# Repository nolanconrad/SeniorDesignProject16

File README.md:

# SeniorDesignProject16
A general area for the code of the Project 16: The Human Cooler

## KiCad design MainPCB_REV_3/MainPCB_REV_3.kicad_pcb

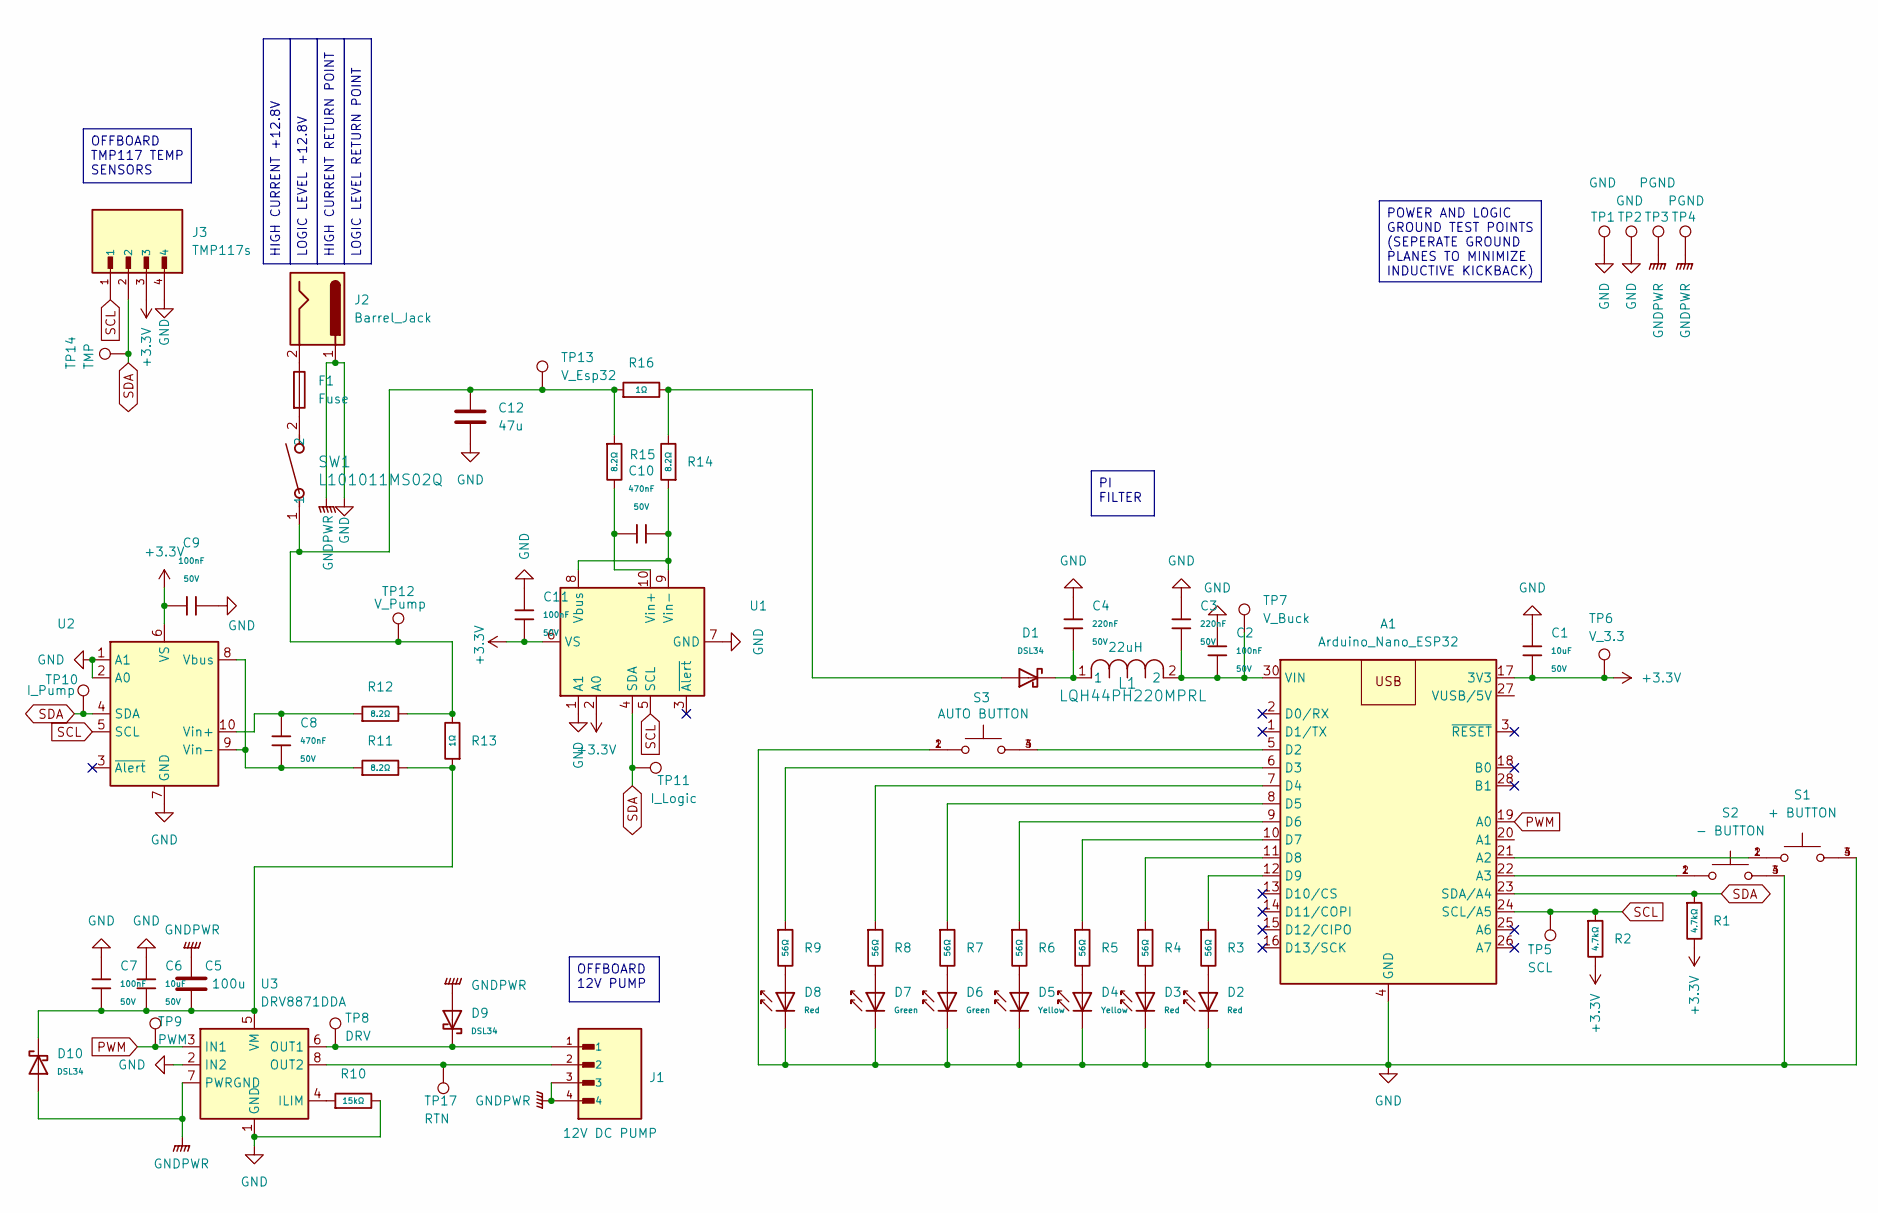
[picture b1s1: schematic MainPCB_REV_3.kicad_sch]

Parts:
A1: Arduino_Nano_ESP32; Arduino_Nano
C1, C6: 10uF; C_1206; Voltage Rated 50V; Tolerance ±10%; Part CL31A106KBHNNNE; LCSC C13585
C2, C7, C9, C11: 100nF; C_1206; Voltage Rated 50V; Tolerance ±10%; Part CL31B104KBCNNNC; LCSC C24497
C3, C4: 220nF; C_1206; Voltage Rated 50V; Tolerance ±10%; Part 1206B224K500NT; LCSC C1857
C5: 100u; CP_Radial_D5.0mm_P2.00mm
C8, C10: 470nF; C_0805; Voltage Rated 50V; Tolerance ±10%; Part CL21B474KBFNNNE; LCSC C13967
C12: 47u; CP_Radial_D5.0mm_P2.00mm
D1, D9, D10: DSL34; D_SOD-123FL; Part DSL34; LCSC C22466347
D2, D3, D8: Red; D_0805; Forward Voltage (VF) 1.6V~2.6V; Part NCD0805R1; LCSC C84256
D4, D5: Yellow; D_0805; Part KT-0805Y; LCSC C2296
D6, D7: Green; D_0805; Part KT-0805G; LCSC C2297
F1: Fuse; FUSE_658_LTF
J1: 12V DC PUMP; JST_S4B-PH-SM4-TB
J2: Barrel_Jack; BarrelJack_CUI_PJ-079BH_Horizontal
J3: TMP117s; JST_S4B-PH-SM4-TB
L1: LQH44PH220MPRL; IND_LQH44PN_PR_MUR
R1, R2: 4.7kΩ; R_1206; Overload Voltage (Max) 200V; Tolerance ±1%; Part 1206W4F4701T5E; LCSC C17936
R3, R4, R5, R6, R7, R8, R9: 56Ω; R_0805; Overload Voltage (Max) 150V; Tolerance ±1%; Part 0805W8F560JT5E; LCSC C17757
R10: 15kΩ; R_0805; Overload Voltage (Max) 150V; Tolerance ±1%; Part 0805W8F1502T5E; LCSC C17475
R11, R12, R14, R15: 8.2Ω; R_1206; Overload Voltage (Max) 200V; Tolerance ±1%; Part 1206W4F100JT5E; LCSC C17903
R13, R16: 1Ω; R_1206; Overload Voltage (Max) 200V; Tolerance ±1%; Part 1206W4F100KT5E; LCSC C17928
S1: + BUTTON; SW_TL3315NF250Q
S2: - BUTTON; SW_TL3315NF250Q
S3: AUTO BUTTON; SW_TL3315NF250Q
SW1: L101011MS02Q; SW_1MS02Q_CNK
TP1, TP2: GND; TestPoint_THTPad_D1.5mm_Drill0.7mm
TP3, TP4: PGND; TestPoint_THTPad_D1.5mm_Drill0.7mm
TP5: SCL; TestPoint_THTPad_D1.5mm_Drill0.7mm
TP6: V_3.3; TestPoint_THTPad_D1.5mm_Drill0.7mm
TP7: V_Buck; TestPoint_THTPad_D1.5mm_Drill0.7mm
TP8: DRV; TestPoint_THTPad_D1.5mm_Drill0.7mm
TP9: PWM; TestPoint_THTPad_D1.5mm_Drill0.7mm
TP10: I_Pump; TestPoint_THTPad_D1.5mm_Drill0.7mm
TP11: I_Logic; TestPoint_THTPad_D1.5mm_Drill0.7mm
TP12: V_Pump; TestPoint_THTPad_D1.5mm_Drill0.7mm
TP13: V_Esp32; TestPoint_THTPad_D1.5mm_Drill0.7mm
TP14: TMP; TestPoint_THTPad_D1.5mm_Drill0.7mm
TP17: RTN; TestPoint_THTPad_D1.5mm_Drill0.7mm
U1, U2: INA226; TSSOP-10_3x3mm_P0.5mm
U3: DRV8871DDA; Texas_HTSOP-8-1EP_3.9x4.9mm_P1.27mm_EP2.95x4.9mm_Mask2.4x3.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

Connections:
+3.3V: A1.17 (3V3), C1.2, C9.2, C11.2, J3.3, R1.2, R2.2, TP6.1 (1_1), U1.2 (A0), U1.6 (VS), U2.6 (VS)
GND: A1.4 (GND), A1.29 (GND), C1.1, C2.1, C3.1, C4.1, C5.2, C6.1, C7.1, C9.1, C11.1, C12.2, D2.1, D3.1, D4.1, D5.1, D6.1, D7.1, D8.1, D9.2, D10.2, J1.3, J1.4, J2.1, J3.4, R10.2, S1.3, S1.4, S2.3, S2.4, S3.1, S3.2, TP1.1 (1_1), TP2.1 (1_1), TP3.1 (1_1), TP4.1 (1_1), U1.1 (A1), U1.7 (GND), U2.1 (A1), U2.2 (A0), U2.7 (GND), U3.1 (GND), U3.2 (IN2), U3.7 (PWRGND), U3.9 (GND)
unnamed: A1.21 (A2), S1.1, S1.2
unnamed: A1.22 (A3), S2.1, S2.2
unnamed: A1.5 (D2), S3.3, S3.4
unnamed: A1.6 (D3), R9.1
unnamed: A1.7 (D4), R8.1
unnamed: A1.8 (D5), R7.1
unnamed: A1.9 (D6), R6.1
unnamed: A1.10 (D7), R5.1
unnamed: A1.11 (D8), R4.1
unnamed: A1.12 (D9), R3.1
unnamed: A1.30 (VIN), C2.2, C3.2, L1.2, TP7.1 (1_1)
unnamed: C4.2, D1.1, L1.1
unnamed: C12.1, R12.2, R13.2, R15.1, R16.1, SW1.1, TP12.1 (1_1), TP13.1 (1_1)
unnamed: D1.2, R14.2, R16.2
unnamed: D2.2, R3.2
unnamed: D3.2, R4.2
unnamed: D4.2, R5.2
unnamed: D5.2, R6.2
unnamed: D6.2, R7.2
unnamed: D7.2, R8.2
unnamed: D8.2, R9.2
unnamed: F1.1, J2.2
unnamed: F1.2, SW1.2
unnamed: C10.2, R14.1, U1.8 (Vbus), U1.9 (Vin-)
unnamed: C10.1, R15.2, U1.10 (Vin+)
unnamed: C8.2, R11.1, U2.8 (Vbus), U2.9 (Vin-)
unnamed: C8.1, R12.1, U2.10 (Vin+)
unnamed: R10.1, U3.4 (ILIM)
unnamed: D9.1, J1.1, TP8.1 (1_1), U3.6 (OUT1)
unnamed: J1.2, TP17.1 (1_1), U3.8 (OUT2)
unnamed: C5.1, C6.2, C7.2, D10.1, R11.2, R13.1, U3.5 (VM)
PWM: A1.19 (A0), TP9.1 (1_1), U3.3 (IN1)
SCL: A1.24 (SCL/A5), J3.1, R2.1, TP5.1 (1_1), U1.5 (SCL), U2.5 (SCL)
SDA: A1.23 (SDA/A4), J3.2, R1.1, TP10.1 (1_1), TP11.1 (1_1), TP14.1 (1_1), U1.4 (SDA), U2.4 (SDA)

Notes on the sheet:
PI FILTER
LOGIC LEVEL +12.8V
HIGH CURRENT RETURN POINT
HIGH CURRENT +12.8V
POWER AND LOGIC GROUND TEST POINTS (SEPERATE GROUND PLANES TO MINIMIZE INDUCTIVE KICKBACK)
OFFBOARD 12V PUMP
LOGIC LEVEL RETURN POINT
OFFBOARD TMP117 TEMP SENSORS

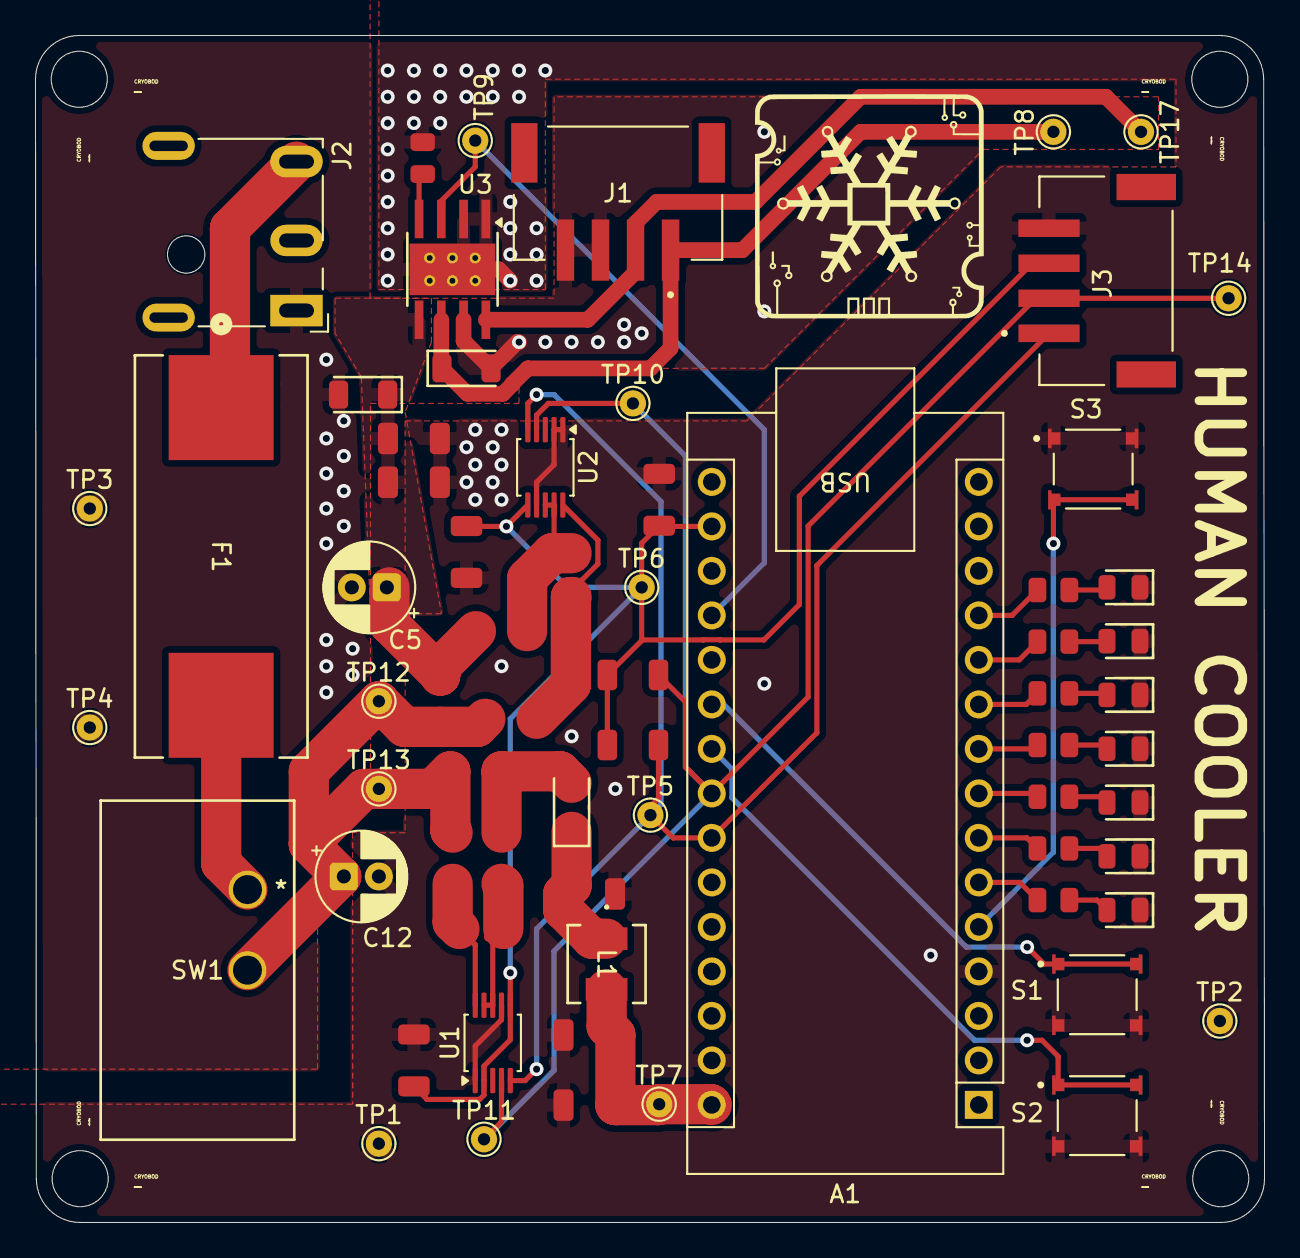
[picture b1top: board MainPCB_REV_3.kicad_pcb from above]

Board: 2 copper layers, 70.2 x 67.8 mm, 66 parts (0 on the bottom side), 36 nets.

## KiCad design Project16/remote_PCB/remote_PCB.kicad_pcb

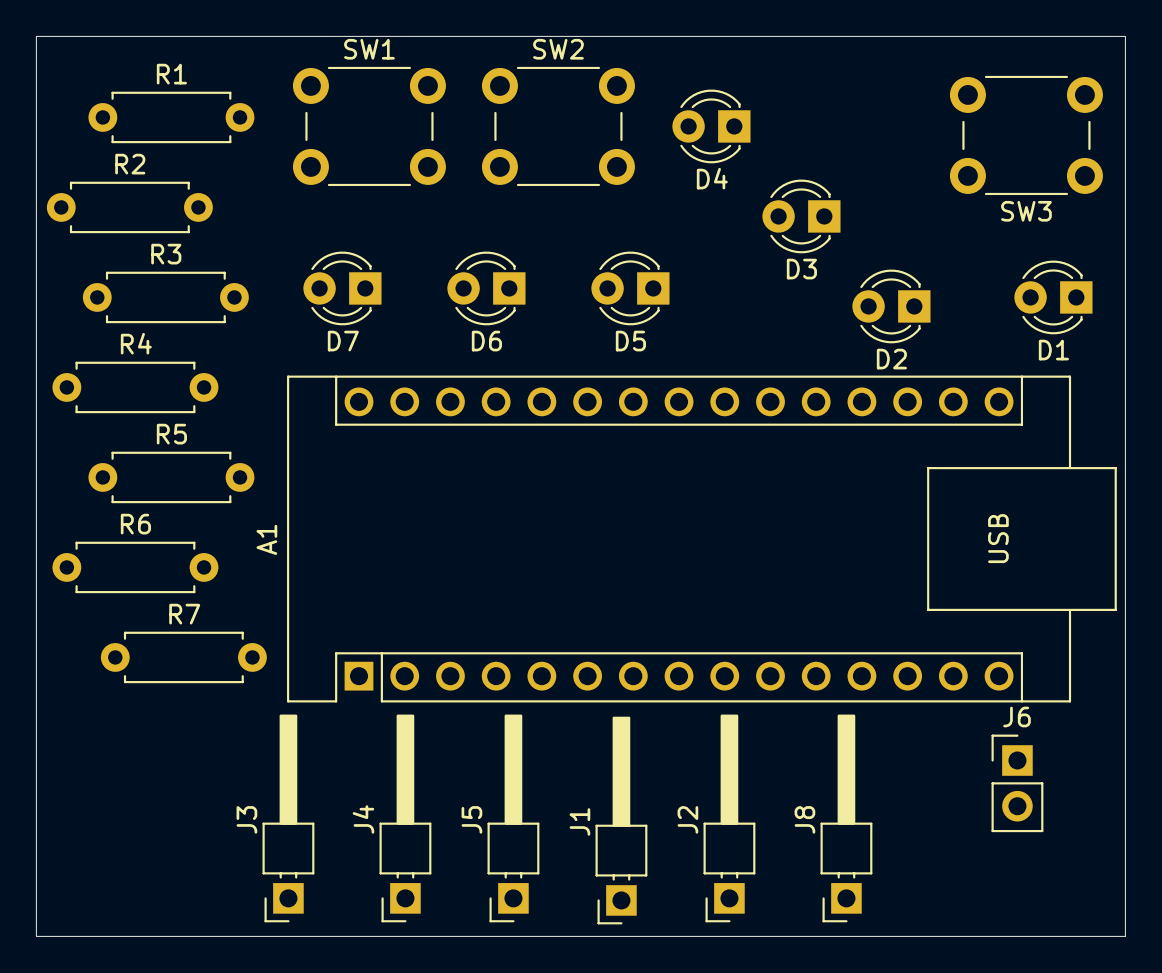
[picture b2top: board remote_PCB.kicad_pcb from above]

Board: 2 copper layers, 60.5 x 50.0 mm, 25 parts (0 on the bottom side), 25 nets, no tracks yet.

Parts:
A1: Arduino_Nano_ESP32; Arduino_Nano
D1: LED Auto; LED_D3.0mm
D2: BAT3; LED_D3.0mm
D3: BAT2; LED_D3.0mm
D4: BAT1; LED_D3.0mm
D5: MAN 3; LED_D3.0mm
D6: MAN 2; LED_D3.0mm
D7: MAN 1; LED_D3.0mm
J1, J2: i2c line; PinHeader_1x01_P2.54mm_Horizontal
J3: Vin; PinHeader_1x01_P2.54mm_Horizontal
J4: VUSB/5V; PinHeader_1x01_P2.54mm_Horizontal
J5: RESET; PinHeader_1x01_P2.54mm_Horizontal
J6: Motor Driver; PinHeader_1x02_P2.54mm_Vertical
J8: Current Sensor; PinHeader_1x01_P2.54mm_Horizontal
R1, R2, R3, R4, R5, R6, R7: R; R_Axial_DIN0207_L6.3mm_D2.5mm_P7.62mm_Horizontal
SW1: Man+; SW_PUSH_6mm
SW2: Man-; SW_PUSH_6mm
SW3: Auto ON/OFF; SW_PUSH_6mm

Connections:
/i2c tmp: A1.5 (D2), A1.6 (D3), J1.1, J2.1
unnamed: A1.19 (A0), J6.2
unnamed: A1.20 (A1), J6.1
unnamed: A1.21 (A2), J8.1
unnamed: A1.25 (A6), SW2.1
unnamed: A1.26 (A7), SW1.2
unnamed: A1.7 (D4), R7.1
unnamed: A1.8 (D5), R6.1
unnamed: A1.9 (D6), R5.1
unnamed: A1.10 (D7), R4.1
unnamed: A1.11 (D8), R3.1
unnamed: A1.12 (D9), R2.1
unnamed: A1.13 (D10/CS), R1.1
unnamed: A1.24 (SCL/A5), SW3.1
unnamed: A1.30 (VIN), J3.1
unnamed: A1.27 (VUSB/5V), J4.1
unnamed: A1.3 (~RESET), J5.1
unnamed: D1.2 (A), R1.2
unnamed: A1.4 (GND), A1.29 (GND), D1.1 (K), D2.1 (K), D3.1 (K), D4.1 (K), D5.1 (K), D6.1 (K), D7.1 (K), SW1.1, SW2.2, SW3.2
unnamed: D2.2 (A), R2.2
unnamed: D3.2 (A), R3.2
unnamed: D4.2 (A), R4.2
unnamed: D5.2 (A), R5.2
unnamed: D6.2 (A), R6.2
unnamed: D7.2 (A), R7.2

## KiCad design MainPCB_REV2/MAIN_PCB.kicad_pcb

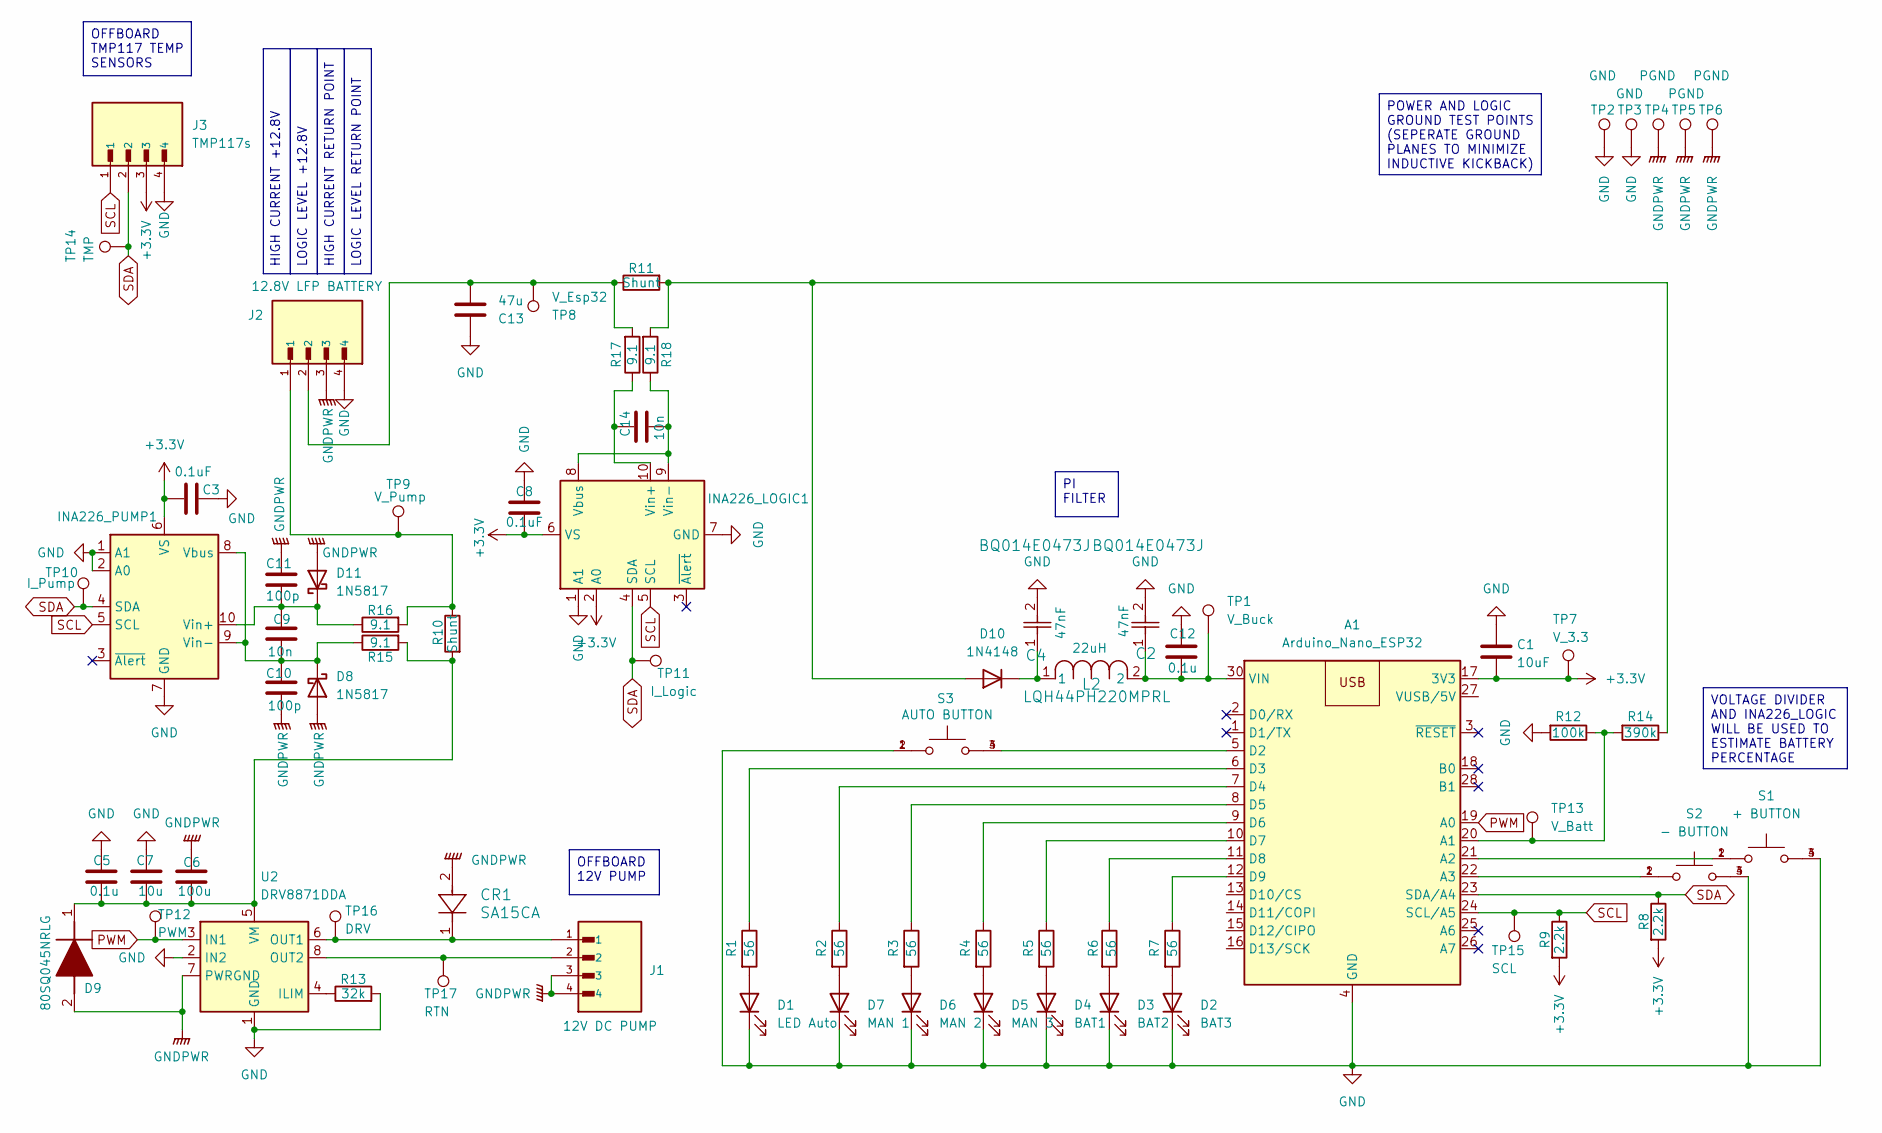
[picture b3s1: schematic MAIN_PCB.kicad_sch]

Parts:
A1: Arduino_Nano_ESP32; Arduino_Nano
C1: 10uF; CP_Radial_D5.0mm_P2.00mm
C2, C4: BQ014E0473J; CAP_BF01_AVX
C3, C8: 0.1uF; CAP_BF01_AVX
C5, C12: 0.1u; CAP_BF01_AVX
C6: 100u; CP_Radial_D5.0mm_P2.00mm
C7: 10u; CP_Radial_D5.0mm_P2.00mm
C9, C14: 10n; C_Rect_L11.0mm_W4.2mm_P10.00mm_MKT
C10, C11: 100p; CAP_BF01_AVX
C13: 47u; CP_Radial_D5.0mm_P2.00mm
CR1: SA15CA; DO-204AC_SA
D1: LED Auto; LED_Oval_W5.2mm_H3.8mm
D2: BAT3; LED_Oval_W5.2mm_H3.8mm
D3: BAT2; LED_Oval_W5.2mm_H3.8mm
D4: BAT1; LED_Oval_W5.2mm_H3.8mm
D5: MAN 3; LED_Oval_W5.2mm_H3.8mm
D6: MAN 2; LED_Oval_W5.2mm_H3.8mm
D7: MAN 1; LED_Oval_W5.2mm_H3.8mm
D8, D11: 1N5817; D_DO-41_SOD81_P10.16mm_Horizontal
D9: 80SQ045NRLG; DIOAD2860W130L840D505; Mouser Part Number 863-80SQ045NRLG
D10: 1N4148; D_DO-35_SOD27_P7.62mm_Horizontal
INA226_LOGIC1, INA226_PUMP1: INA226; VSSOP-10_3x3mm_P0.5mm
J1: 12V DC PUMP; JST_S4B-PH-SM4-TB
J2: 12.8V LFP BATTERY; JST_S4B-PH-SM4-TB
J3: TMP117s; JST_S4B-PH-SM4-TB
L2: LQH44PH220MPRL; IND_LQH44PN_PR_MUR
R1, R2, R3, R4, R5, R6, R7: 56; R_Axial_DIN0207_L6.3mm_D2.5mm_P10.16mm_Horizontal
R8, R9: 2.2k; R_Axial_DIN0207_L6.3mm_D2.5mm_P10.16mm_Horizontal
R10, R11: Shunt; R_1206_3216Metric
R12: 100k; R_Axial_DIN0207_L6.3mm_D2.5mm_P10.16mm_Horizontal
R13: 32k; R_Axial_DIN0207_L6.3mm_D2.5mm_P10.16mm_Horizontal
R14: 390k; R_Axial_DIN0207_L6.3mm_D2.5mm_P10.16mm_Horizontal
R15, R16, R17, R18: 9.1; R_Axial_DIN0207_L6.3mm_D2.5mm_P10.16mm_Horizontal
S1: + BUTTON; SW_B3F-1000
S2: - BUTTON; SW_B3F-1000
S3: AUTO BUTTON; SW_B3F-1000
TP1: V_Buck; TestPoint_THTPad_D1.5mm_Drill0.7mm
TP2, TP3: GND; TestPoint_THTPad_D1.5mm_Drill0.7mm
TP4, TP5, TP6: PGND; TestPoint_THTPad_D1.5mm_Drill0.7mm
TP7: V_3.3; TestPoint_THTPad_D1.5mm_Drill0.7mm
TP8: V_Esp32; TestPoint_THTPad_D1.5mm_Drill0.7mm
TP9: V_Pump; TestPoint_THTPad_D1.5mm_Drill0.7mm
TP10: I_Pump; TestPoint_THTPad_D1.5mm_Drill0.7mm
TP11: I_Logic; TestPoint_THTPad_D1.5mm_Drill0.7mm
TP12: PWM; TestPoint_THTPad_D1.5mm_Drill0.7mm
TP13: V_Batt; TestPoint_THTPad_D1.5mm_Drill0.7mm
TP14: TMP; TestPoint_THTPad_D1.5mm_Drill0.7mm
TP15: SCL; TestPoint_THTPad_D1.5mm_Drill0.7mm
TP16: DRV; TestPoint_THTPad_D1.5mm_Drill0.7mm
TP17: RTN; TestPoint_THTPad_D1.5mm_Drill0.7mm
U2: DRV8871DDA; Texas_HTSOP-8-1EP_3.9x4.9mm_P1.27mm_EP2.95x4.9mm_Mask2.4x3.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

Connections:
+3.3V: A1.17 (3V3), C1.1, C3.2, C8.2, INA226_LOGIC1.2 (A0), INA226_LOGIC1.6 (VS), INA226_PUMP1.6 (VS), J3.3, R8.2, R9.2, TP7.1
GND: A1.4 (GND), A1.29 (GND), C1.2, C2.2, C3.1, C4.2, C5.1, C7.2, C8.1, C12.1, C13.2, D1.1 (K), D2.1 (K), D3.1 (K), D4.1 (K), D5.1 (K), D6.1 (K), D7.1 (K), INA226_LOGIC1.1 (A1), INA226_LOGIC1.7 (GND), INA226_PUMP1.1 (A1), INA226_PUMP1.2 (A0), INA226_PUMP1.7 (GND), J2.4, J3.4, R12.2, R13.2, S1.3, S1.4, S2.3, S2.4, S3.1, S3.2, TP2.1, TP3.1, U2.1 (GND), U2.2 (IN2), U2.9 (GND)
GNDPWR: C6.2, C10.1, C11.2, CR1.2, D8.2 (A), D9.2 (A), D11.2 (A), J1.3, J1.4, J2.3, TP4.1, TP5.1, TP6.1, U2.7 (PWRGND)
unnamed: A1.20 (A1), R12.1, R14.2, TP13.1
unnamed: A1.21 (A2), S1.1, S1.2
unnamed: A1.22 (A3), S2.1, S2.2
unnamed: A1.5 (D2), S3.3, S3.4
unnamed: A1.6 (D3), R1.1
unnamed: A1.7 (D4), R2.1
unnamed: A1.8 (D5), R3.1
unnamed: A1.9 (D6), R4.1
unnamed: A1.10 (D7), R5.1
unnamed: A1.11 (D8), R6.1
unnamed: A1.12 (D9), R7.1
unnamed: A1.30 (VIN), C2.1, C12.2, L2.2, TP1.1
unnamed: C13.1, J2.2, R11.1, R17.2, TP8.1
unnamed: D1.2 (A), R1.2
unnamed: D2.2 (A), R7.2
unnamed: D3.2 (A), R6.2
unnamed: D4.2 (A), R5.2
unnamed: D5.2 (A), R4.2
unnamed: D6.2 (A), R3.2
unnamed: D7.2 (A), R2.2
unnamed: C9.1, C10.2, D8.1 (K), INA226_PUMP1.8 (Vbus), INA226_PUMP1.9 (Vin-), R15.1
unnamed: C5.2, C6.1, C7.1, D9.1 (K), R10.2, R15.2, U2.5 (VM)
unnamed: D10.2 (A), R11.2, R14.1, R18.2
unnamed: C4.1, D10.1 (K), L2.1
unnamed: C9.2, C11.1, D11.1 (K), INA226_PUMP1.10 (Vin+), R16.1
unnamed: C14.1, INA226_LOGIC1.8 (Vbus), INA226_LOGIC1.9 (Vin-), R18.1
unnamed: C14.2, INA226_LOGIC1.10 (Vin+), R17.1
unnamed: J2.1, R10.1, R16.2, TP9.1
unnamed: R13.1, U2.4 (ILIM)
unnamed: CR1.1, J1.1, TP16.1, U2.6 (OUT1)
unnamed: J1.2, TP17.1, U2.8 (OUT2)
PWM: A1.19 (A0), TP12.1, U2.3 (IN1)
SCL: A1.24 (SCL/A5), INA226_LOGIC1.5 (SCL), INA226_PUMP1.5 (SCL), J3.1, R9.1, TP15.1
SDA: A1.23 (SDA/A4), INA226_LOGIC1.4 (SDA), INA226_PUMP1.4 (SDA), J3.2, R8.1, TP10.1, TP11.1, TP14.1

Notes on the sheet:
LOGIC LEVEL RETURN POINT
OFFBOARD 12V PUMP
POWER AND LOGIC GROUND TEST POINTS (SEPERATE GROUND PLANES TO MINIMIZE INDUCTIVE KICKBACK)
OFFBOARD TMP117 TEMP SENSORS
PI FILTER
VOLTAGE DIVIDER AND INA226_LOGIC WILL BE USED TO ESTIMATE BATTERY PERCENTAGE
HIGH CURRENT +12.8V
LOGIC LEVEL +12.8V
HIGH CURRENT RETURN POINT

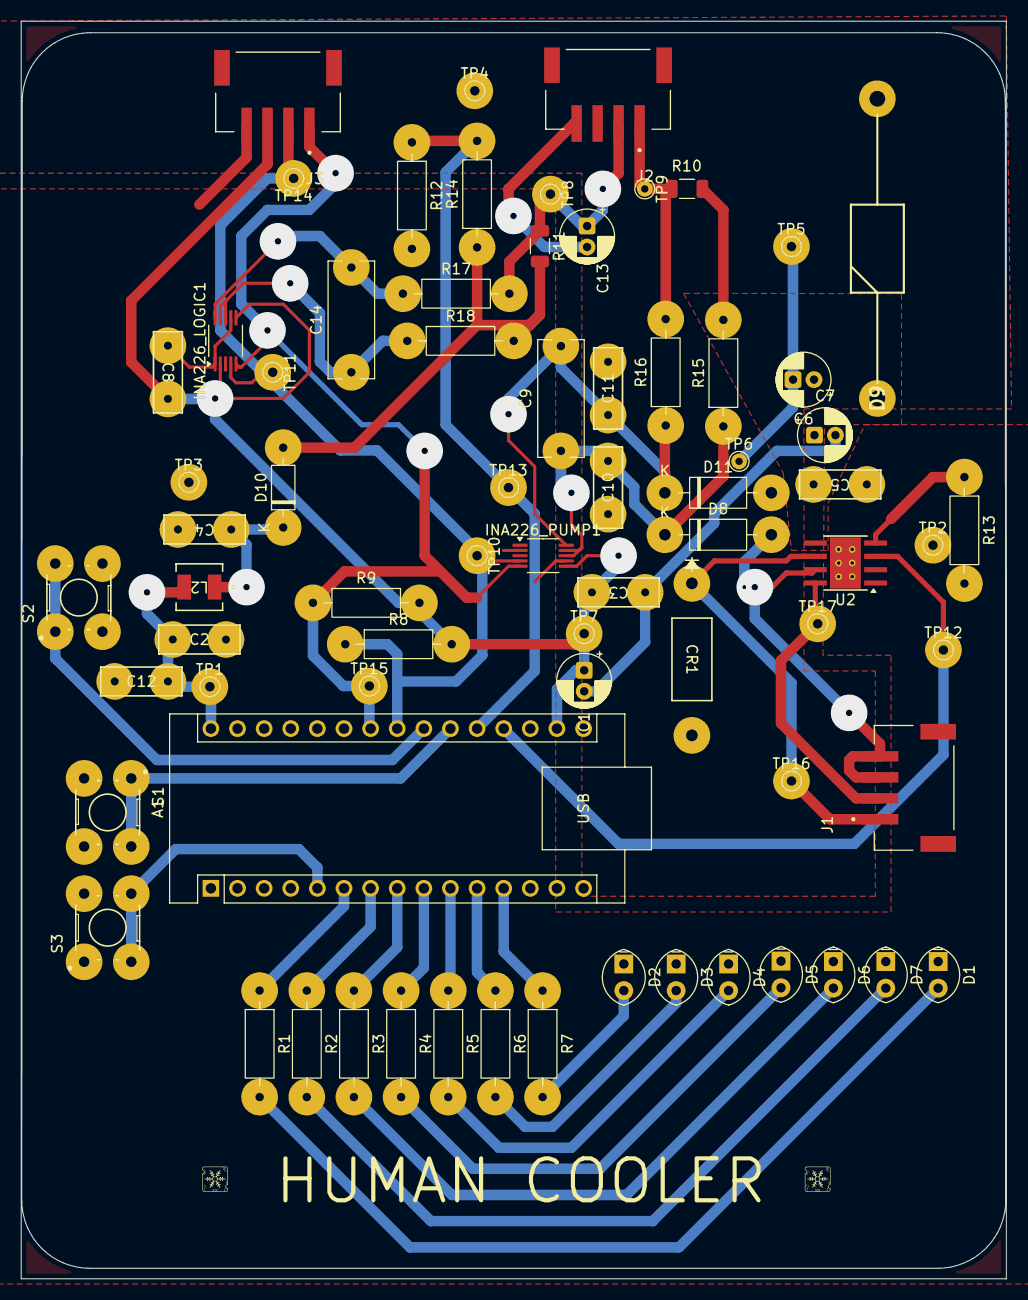
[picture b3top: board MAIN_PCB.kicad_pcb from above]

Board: 2 copper layers, 94.0 x 120.0 mm, 72 parts (0 on the bottom side), 37 nets.

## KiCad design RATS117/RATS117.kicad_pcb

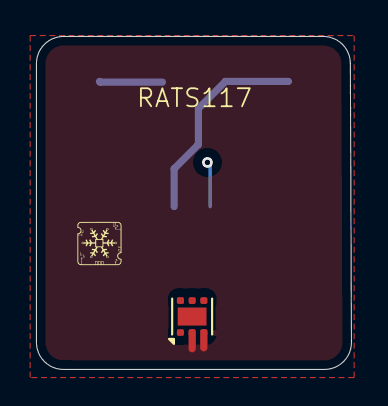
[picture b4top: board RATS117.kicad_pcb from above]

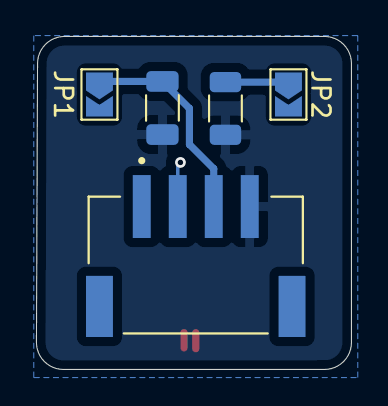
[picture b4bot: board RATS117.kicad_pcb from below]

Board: 2 copper layers, 17.5 x 18.5 mm, 6 parts (5 on the bottom side), 5 nets.

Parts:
C1: 0.1uF; C_1206_3216Metric
J1: S4B-PH-SM4-TB; JST_S4B-PH-SM4-TB
JP1, JP2: SolderJumper_2_Open; SolderJumper-2_P1.3mm_Open_TrianglePad1.0x1.5mm
R1: 47k; R_1206_3216Metric
U1: TMP117xxDRV; WSON-6-1EP_2x2mm_P0.65mm_EP1x1.6mm

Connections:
GND: C1.1, J1.4, R1.2, U1.2 (GND), U1.3 (ALERT)
unnamed: JP1.2 (B), JP2.1 (A), R1.1, U1.4 (ADD0)
unnamed: J1.2, JP2.2 (B), U1.6 (SDA)
unnamed: J1.1, U1.1 (SCL)
VCC: C1.2, J1.3, JP1.1 (A), U1.5 (V+)

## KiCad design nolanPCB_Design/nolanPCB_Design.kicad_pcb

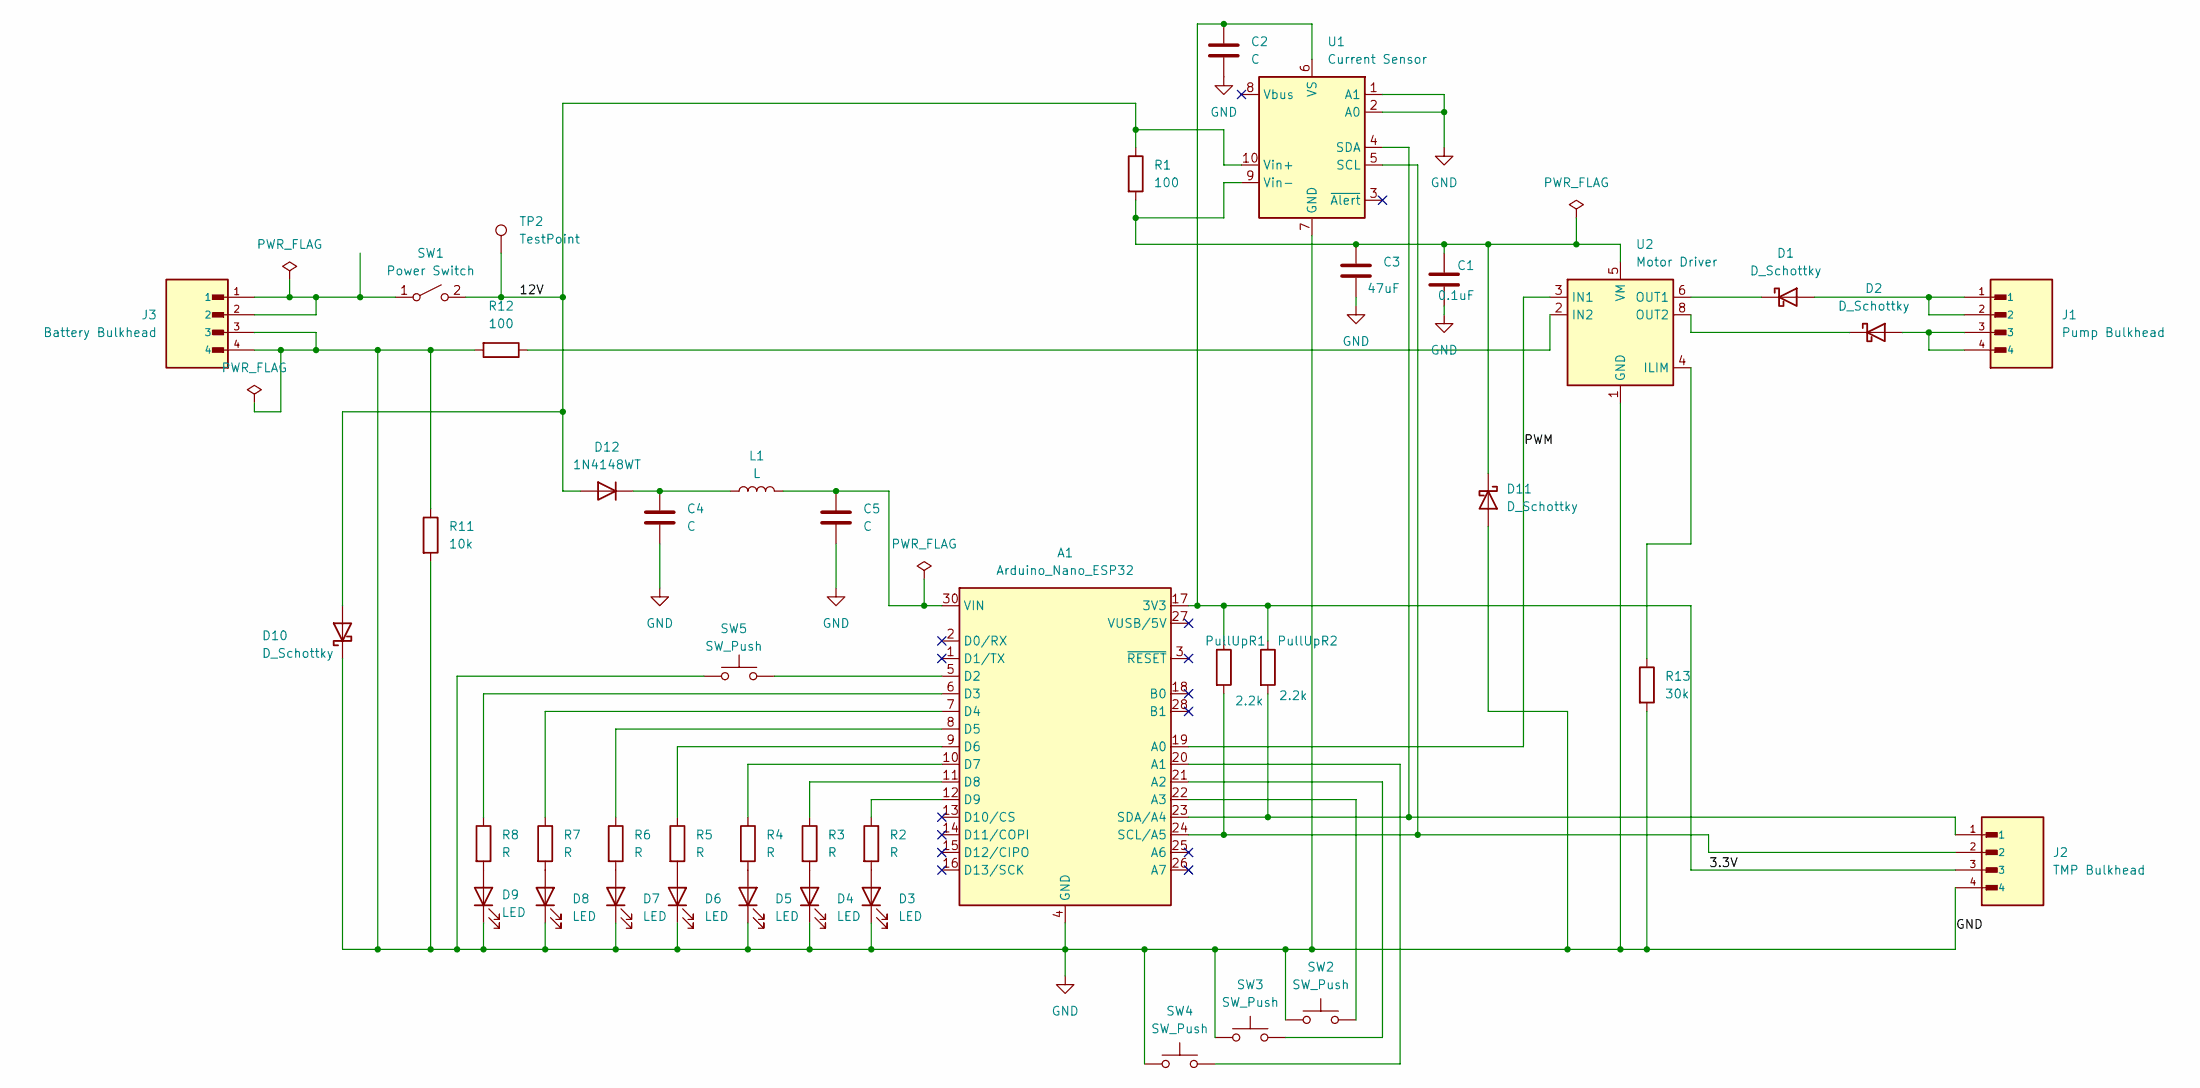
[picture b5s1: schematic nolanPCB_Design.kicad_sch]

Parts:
A1: Arduino_Nano_ESP32; Arduino_Nano
C1: 0.1uF; C_Disc_D5.0mm_W2.5mm_P5.00mm
C2: C; C_Disc_D7.5mm_W2.5mm_P5.00mm
C3: 47uF; C_Radial_D6.3mm_H11.0mm_P2.50mm
C4, C5: C; C_Radial_D6.3mm_H11.0mm_P2.50mm
D1, D2, D10, D11: D_Schottky; D_DO-41_SOD81_P10.16mm_Horizontal
D3, D4, D5, D6, D7, D8, D9: LED; LED_D5.0mm
D12: 1N4148WT; D_SOD-523
J1: Pump Bulkhead; JST_PH_S4B-PH-SM4-TB_1x04-1MP_P2.00mm_Horizontal
J2: TMP Bulkhead; JST_PH_S4B-PH-SM4-TB_1x04-1MP_P2.00mm_Horizontal
J3: Battery Bulkhead; JST_PH_S4B-PH-SM4-TB_1x04-1MP_P2.00mm_Horizontal
L1: L; IND_LQH44PN_PR_MUR
PullUpR1: 2.2k; R_Axial_DIN0207_L6.3mm_D2.5mm_P7.62mm_Horizontal
PullUpR2: 2.2k; R_Axial_DIN0411_L9.9mm_D3.6mm_P12.70mm_Horizontal
R1, R12: 100; R_Axial_DIN0411_L9.9mm_D3.6mm_P12.70mm_Horizontal
R2, R3, R4, R5, R6, R7, R8: R; R_Axial_DIN0411_L9.9mm_D3.6mm_P12.70mm_Horizontal
R11: 10k; R_Axial_DIN0411_L9.9mm_D3.6mm_P12.70mm_Horizontal
R13: 30k; R_Axial_DIN0411_L9.9mm_D3.6mm_P12.70mm_Horizontal
SW1: Power Switch; SW_PRK22J5DBBNN_ZFE
SW2, SW3, SW4, SW5: SW_Push; SW_PUSH_6mm
TP2: TestPoint; TestPoint_THTPad_D1.5mm_Drill0.7mm
U1: Current Sensor; VSSOP-10_3x3mm_P0.5mm
U2: Motor Driver; Texas_HTSOP-8-1EP_3.9x4.9mm_P1.27mm_EP2.95x4.9mm_Mask2.4x3.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

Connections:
/3.3V: A1.17 (3V3), C2.1, J2.3, PullUpR1.1, PullUpR2.1, U1.6 (VS)
/12V: D10.2 (A), D12.2 (A), R1.1, SW1.2 (B), TP2.1, U1.10 (Vin+)
/PWM: A1.19 (A0), U2.3 (IN1); also elsewhere on the board
GND: A1.4 (GND), A1.29 (GND), C1.2, C2.2, C3.2, C4.2, C5.2, D3.1 (K), D4.1 (K), D5.1 (K), D6.1 (K), D7.1 (K), D8.1 (K), D9.1 (K), D10.1 (K), D11.2 (A), J2.4, J3.3, J3.4, R11.1, R11.2, R12.2, R13.2, SW2.1, SW3.1, SW4.1, SW5.1, U1.1 (A1), U1.2 (A0), U1.7 (GND), U2.1 (GND), U2.7 (GND), U2.9 (GND); also elsewhere on the board
unnamed: A1.20 (A1), SW4.2
unnamed: A1.21 (A2), SW3.2
unnamed: A1.22 (A3), SW2.2
unnamed: A1.5 (D2), SW5.2
unnamed: A1.6 (D3), R8.1
unnamed: A1.7 (D4), R7.1
unnamed: A1.8 (D5), R6.1
unnamed: A1.9 (D6), R5.1
unnamed: A1.10 (D7), R4.1
unnamed: A1.11 (D8), R3.1
unnamed: A1.12 (D9), R2.1
unnamed: A1.24 (SCL/A5), J2.2, PullUpR1.2, U1.5 (SCL)
unnamed: A1.23 (SDA/A4), J2.1, PullUpR2.2, U1.4 (SDA)
unnamed: A1.30 (VIN), C5.1, L1.2
unnamed: D1.2 (A), J1.1, J1.2
unnamed: D1.1 (K), U2.6 (OUT1)
unnamed: D2.2 (A), J1.3, J1.4
unnamed: D2.1 (K), U2.8 (OUT2)
unnamed: D3.2 (A), R2.2
unnamed: D4.2 (A), R3.2
unnamed: D5.2 (A), R4.2
unnamed: D6.2 (A), R5.2
unnamed: D7.2 (A), R6.2
unnamed: D8.2 (A), R7.2
unnamed: D9.2 (A), R8.2
unnamed: C1.1, C3.1, D11.1 (K), R1.2, U1.9 (Vin-), U2.5 (VM)
unnamed: C4.1, D12.1 (K), L1.1
unnamed 31: J3.1, J3.2, SW1.1 (A); also elsewhere on the board
unnamed: R13.1, U2.4 (ILIM)
unnamed: R12.1, U2.2 (IN2)

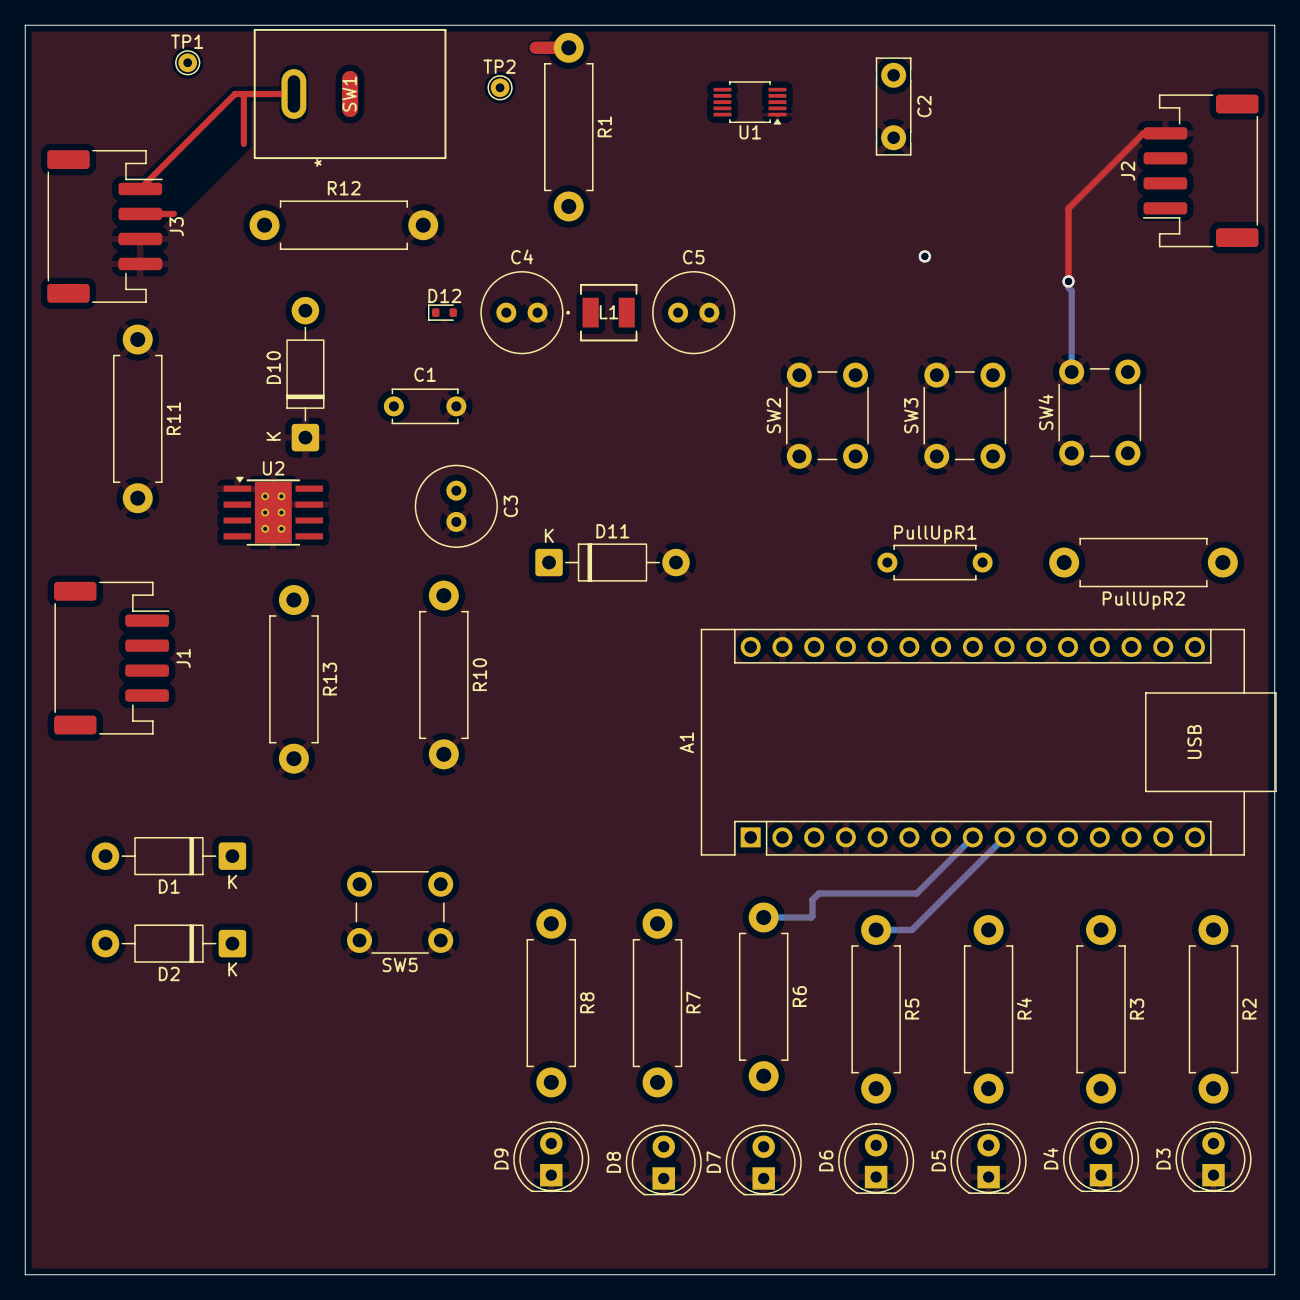
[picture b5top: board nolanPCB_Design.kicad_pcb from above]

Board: 2 copper layers, 100.0 x 100.0 mm, 45 parts (0 on the bottom side), 34 nets.

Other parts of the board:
R10: 10k; R_Axial_DIN0411_L9.9mm_D3.6mm_P12.70mm_Horizontal
TP1: TestPoint; TestPoint_THTPad_D1.5mm_Drill0.7mm

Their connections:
/PWM: R10.1; also elsewhere on the board
GND: R10.2; also elsewhere on the board
unnamed 31: TP1.1; also elsewhere on the board
